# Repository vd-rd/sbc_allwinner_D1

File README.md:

### Features
 * CPU - Allwinner D1 processor (RISC-V C906 @ 1GHz)
 * RAM - 16Gb DDR3L max
 * microSD card slot
 * microUSB OTG port
 * RGMII interface for Ethernet
 * LCD interface
 * standard Apollo.IoT expansion header

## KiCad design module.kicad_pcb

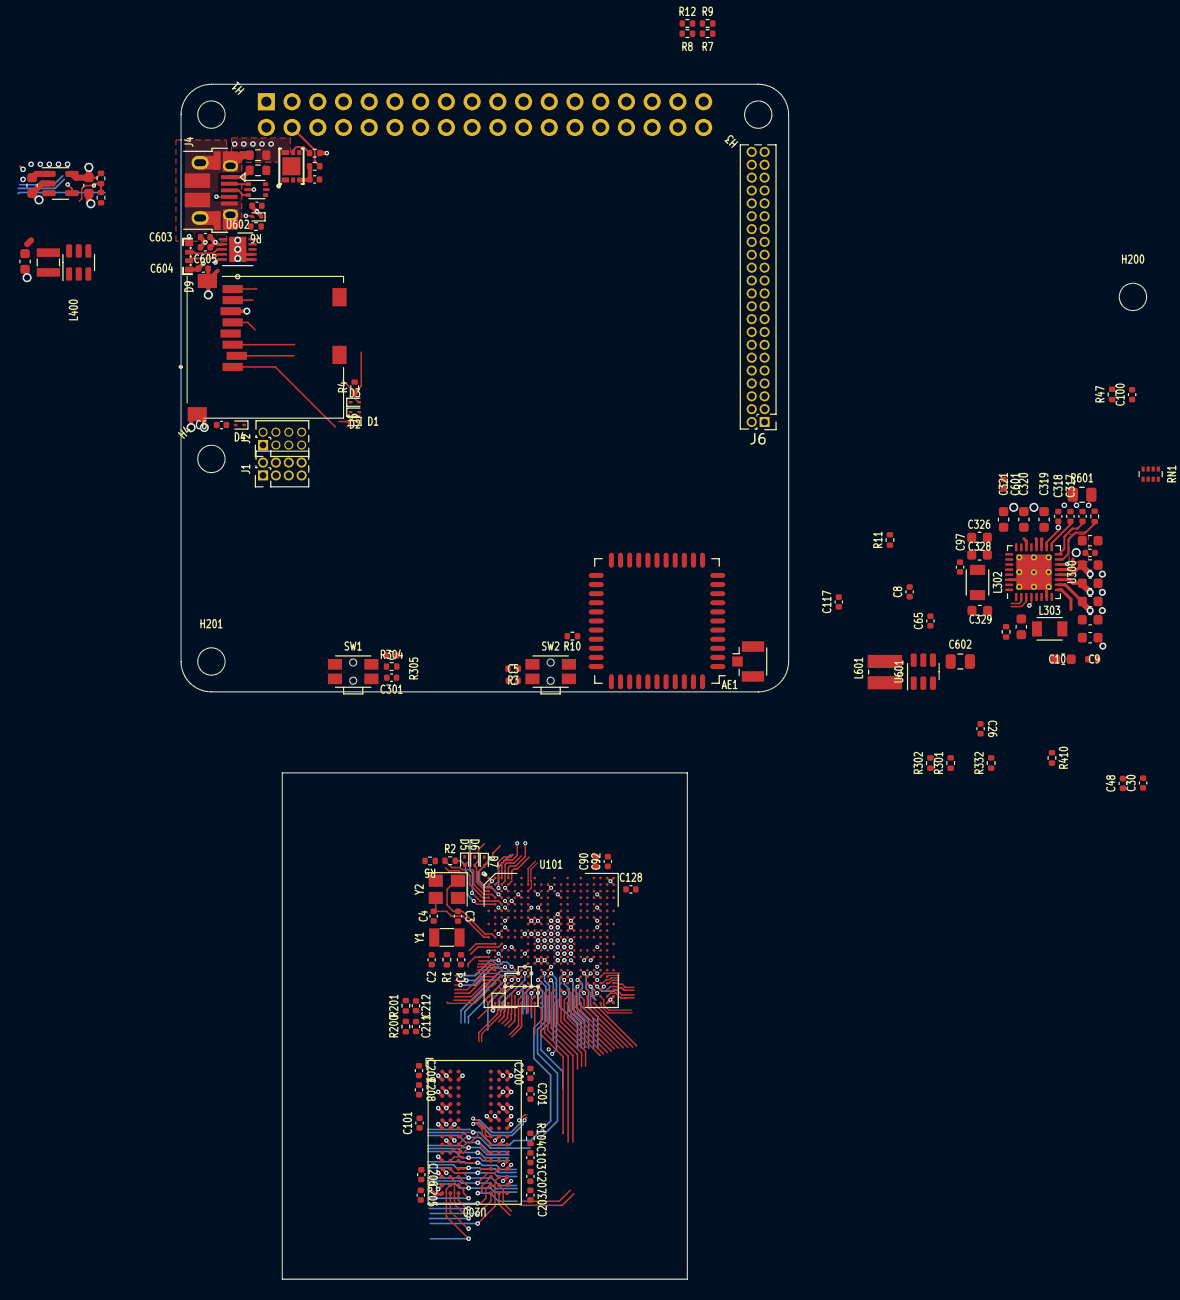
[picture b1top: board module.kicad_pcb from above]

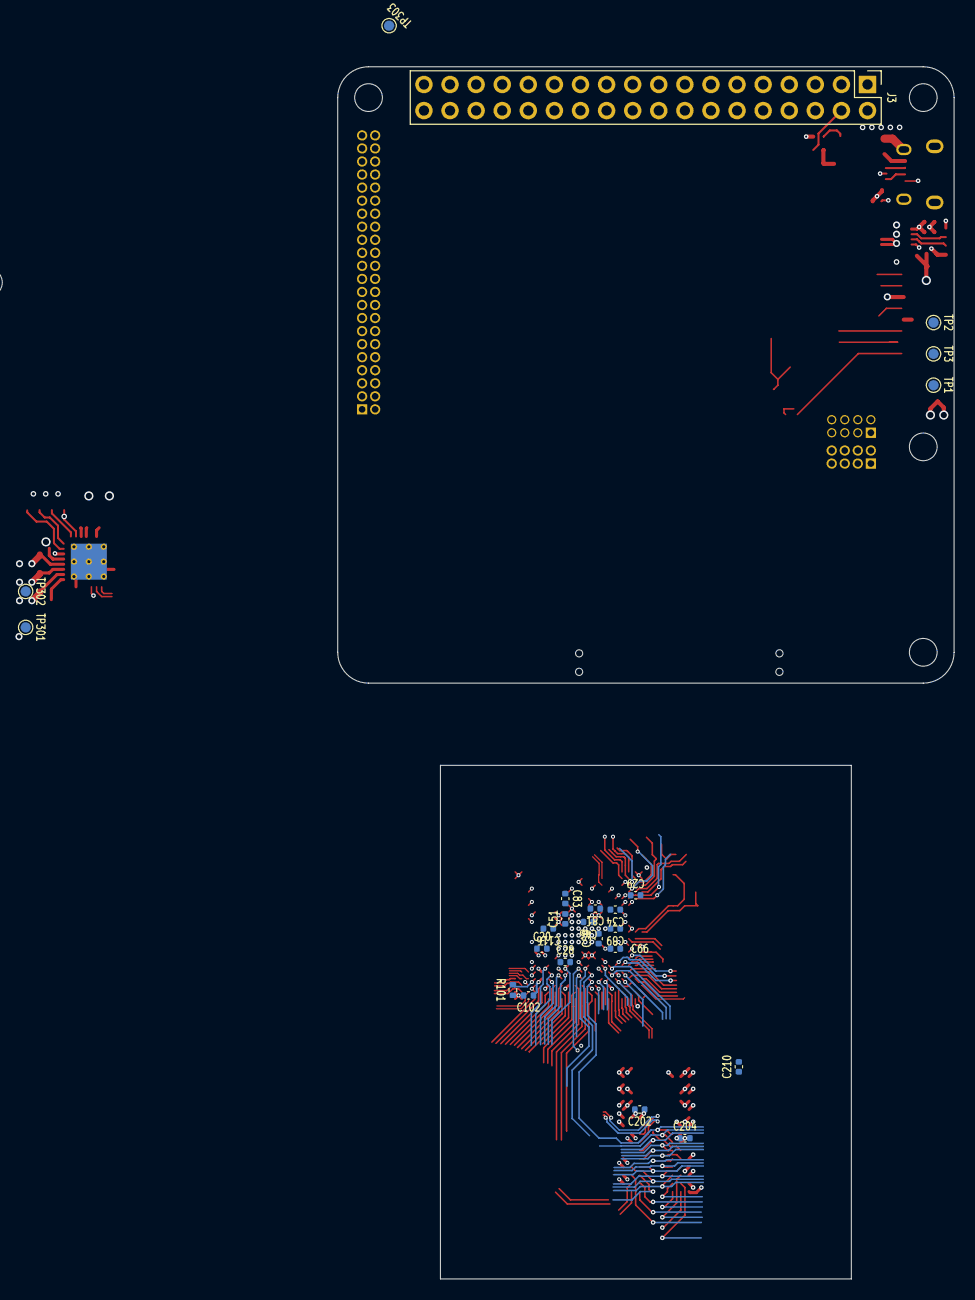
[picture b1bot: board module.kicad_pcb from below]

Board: 4 copper layers, 60.0 x 118.0 mm, 153 parts (24 on the bottom side), 179 nets.

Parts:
AE1: Antenna_Shield; U.FL_Hirose_U.FL-R-SMT-1_Vertical
C1, C2: 15pF; C_0402_1005Metric
C3, C4: 22pF; C_0402_1005Metric
C5, C7, C8, C10, C20, C26, C28, C29, C30, C34, C46, C48, C50, C51, C65, C66, C81, C83, C89, C97, C100, C101, C102, C103, C116, C117, C128, C200, C201, C202, C203, C204, C205, C206, C207, C208, C209, C210, C211, C212, C301, C501, C604, C3131: 100nF; C_0402_1005Metric
C6: 10uF; C_0402_1005Metric
C9, C309, C310, C312, C313: 4.7uF; C_0603_1608Metric
C90, C92: 470nF; C_0402_1005Metric
C305, C308, C311, C319, C320, C321, C326, C328, C329, C400, C410, C411: 10uF; C_0603_1608Metric
C316, C317, C318, C601, C603, C605: 1uF; C_0402_1005Metric
C602: C_Small; C_0805_2012Metric
D1, D2, D3, D4, D5, D6, D7: 3V3; D_SOD-923
D8: 5V; D_SOD-923
D9: LED_RGBA; rgb-1204
FB1, FB2: FerriteBead_Small; R_0603_1608Metric
H1, H3, H4, H200, H201: MountingHole; MountingHole_2.7mm_M2.5
J1, J2: Conn_01x08; PinHeader_2x04_P1.27mm_Vertical
J3: Conn_02x18_Odd_Even; PinHeader_2x18_P2.54mm_Vertical
J4: USB_B_Micro; USB_Micro-B_Amphenol_10103594-0001LF_Horizontal
J5: Micro_SD_Card_Det; MEM20610118800A
J6: Conn_02x22_Odd_Even; PinHeader_2x22_P1.27mm_Vertical
L302, L303: 4.7uH; L_TDK_NLV25_2.5x2.0mm
L400: L_Small; L_Wuerth_MAPI-2510
L601: 22uH; L_Wuerth_MAPI-3010
R1: 10M; R_0402_1005Metric
R2: 33; R_0402_1005Metric
R3, R305: 1k; R_0402_1005Metric
R4, R5, R6, R302, R303: 10k; R_0402_1005Metric
R7, R8, R9, R12, R304: 47k; R_0402_1005Metric
R10, R11: 22; R_0402_1005Metric
R47, R101, R104: 240; R_0402_1005Metric
R200, R201, R301: 2.2k; R_0402_1005Metric
R315: 200K; R_0402_1005Metric
R332: 10K; R_0402_1005Metric
R401: 976k; R_0402_1005Metric
R402: 562k; R_0402_1005Metric
R410: 100K; R_0402_1005Metric
R501: 330; R_0402_1005Metric
R502: 2.7k; R_0402_1005Metric
R601: 10; R_0805_2012Metric
RN1: 47k; R_Array_Concave_4x0402
SW1, SW2: SW_Push; SW_SPST_EVQP7C
TP1, TP2, TP3, TP301, TP302, TP303: TestPoint; TestPoint_Pad_D1.0mm
U1: USBLC6-2P6; SOT-666
U100: AP6255; lga44_12x12mm_P0.9
U101: D1; BGA-337_20x20_13.0x13.0mm
U200: DDR3L-x16; BGA-96_9x14mm_P0.8mm
U300: AXP173; VQFN-32-1EP_5x5mm_P0.5mm_EP3.5x3.5mm_ThermalVias
U400: MCP1640CH; SOT-23-6
U410: AP22811; SOT-23-5
U500: AP9211; DFN-2030-6
U601: AP3019; SOT-23-6
U602: IS31FL3193; DFN-10-1EP_3x3mm_P0.5mm_EP1.7x2.5mm
Y1: 32.768kHz; Crystal_SMD_3215-2Pin_3.2x1.5mm
Y2: 24M; Crystal_SMD_3225-4Pin_3.2x2.5mm

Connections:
+1V8_LDO: C20.1, C28.1, C50.1, C65.1, C89.1, C97.1, C301.1, R304.2, U101.J4 (VCC-EFUSE), U101.L7 (LDOA-OUT), U101.M17 (VCC-HDMI), U101.P14 (VDD18-DRAM), U101.R16 (VCC-LVDS)
+1V35: C200.1, C201.1, C202.1, C203.1, C204.1, C205.1, C206.1, C207.1, C208.1, C209.1, C210.1, C211.1, R200.1, U200.A1 (VDDQ), U200.A8 (VDDQ), U200.B2 (VDD), U200.C1 (VDDQ), U200.C9 (VDDQ), U200.D2 (VDDQ), U200.D9 (VDD), U200.E9 (VDDQ), U200.F1 (VDDQ), U200.G7 (VDD), U200.H2 (VDDQ), U200.H9 (VDDQ), U200.K2 (VDD), U200.K8 (VDD), U200.N1 (VDD), U200.N9 (VDD), U200.R1 (VDD), U200.R9 (VDD)
+3V0: C310.1, TP302.1, U300.10 (LDO2)
+3V3: C6.1, C29.1, C34.1, C66.1, C83.1, C128.1, C329.1, C603.1, C604.1, C605.1, D4.2 (A2), D9.4 (A), J3.2, J5.P4 (VDD), J6.43, L302.2, R4.2, R5.2, R6.2, R7.2, R9.2, R301.1, R302.1, R303.1, TP303.1, U101.C20 (VDD33), U101.D12 (HPLDOIN), U101.E4 (VCC-PG), U101.G4 (VCC-PC), U101.G17 (VCC-IO), U101.M7 (LDO-IN), U101.T16 (VCC-PD), U300.31 (DCDC1), U602.2 (VCC)
+3V3_LDO: C312.1, J6.8, U300.12 (LDO4)
+5V_USB: C7.1, C319.1, C411.1, FB2.2, U1.5 (VBUS), U300.19 (VBUS), U410.1 (OUT)
/cpu/hse-in: C4.1, U101.K1 (DXIN), Y2.3
/cpu/hse-out: C3.1, U101.K2 (DXOUT), Y2.1
/cpu/lse-in: C1.1, R1.1, U101.L2 (X32KIN), Y1.1
/cpu/lse-out: C2.1, R1.2, U101.L3 (X32KOUT), Y1.2
/cpu/vcc-dram: C30.1, C48.1
/cpu/vra1: C92.1, U101.B19 (VRA1)
/cpu/vra2: C90.1, U101.B18 (VRA2)
/io/uart0: D5.2 (A2), J5.P5 (CLK), R2.2, TP1.1
/io/usb+: J4.3 (D+), U1.3 (I/O2)
/io/usb-: J4.2 (D-), U1.1 (I/O1)
/io/usb_gnd: FB1.1, J4.5 (GND), J4.6 (Shield)
/memory/ddr-a0: U101.V13 (SA0), U200.N3 (A0)
/memory/ddr-a1: U101.W13 (SA1), U200.P7 (A1)
/memory/ddr-a2: U101.V14 (SA2), U200.P3 (A2)
/memory/ddr-a3: U101.U13 (SA3), U200.N2 (A3)
/memory/ddr-a4: U101.U15 (SA4), U200.P8 (A4)
/memory/ddr-a5: U101.V11 (SA5), U200.P2 (A5)
/memory/ddr-a6: U101.W11 (SA6), U200.R8 (A6)
/memory/ddr-a7: U101.Y13 (SA7), U200.R2 (A7)
/memory/ddr-a8: U101.W14 (SA8), U200.T8 (A8)
/memory/ddr-a9: U101.Y15 (SA9), U200.R3 (A9)
/memory/ddr-a10: U101.W12 (SA10), U200.L7 (A10/AP)
/memory/ddr-a11: U101.W15 (SA11), U200.R7 (A11)
/memory/ddr-a12: U101.W16 (SA12), U200.N7 (A12/~BC)
/memory/ddr-a13: U101.R15 (SA13), U200.T3 (A13)
/memory/ddr-a14: U101.V16 (SA14), U200.T7 (A14)
/memory/ddr-a15: U101.T15 (SA15), U200.M7 (A15(nc))
/memory/ddr-ba0: U101.V10 (SBA0), U200.M2 (BA0)
/memory/ddr-ba1: U101.W10 (SBA1), U200.N8 (BA1)
/memory/ddr-ba2: U101.Y11 (SBA2), U200.M3 (BA2)
/memory/ddr-cas: U101.T9 (SCAS), U200.K3 (~CAS)
/memory/ddr-cke0: U101.W9 (SCKE0), U200.K9 (CKE)
/memory/ddr-cs0: U101.R12 (SCS0), U200.L2 (~CS)
/memory/ddr-d0: U101.W7 (SDQ0), U200.E3 (DQL0)
/memory/ddr-d1: U101.V7 (SDQ1), U200.F7 (DQL1)
/memory/ddr-d2: U101.W8 (SDQ2), U200.F2 (DQL2)
/memory/ddr-d3: U101.V8 (SDQ3), U200.F8 (DQL3)
/memory/ddr-d4: U101.W4 (SDQ4), U200.H3 (DQL4)
/memory/ddr-d5: U101.Y4 (SDQ5), U200.H7 (DQL7)
/memory/ddr-d6: U101.V5 (SDQ6), U200.G2 (DQL6)
/memory/ddr-d7: U101.W5 (SDQ7), U200.H8 (DQL5)
/memory/ddr-d8: U101.U4 (SDQ8), U200.D7 (DQU0)
/memory/ddr-d9: U101.U7 (SDQ9), U200.C3 (DQU1)
/memory/ddr-d10: U101.U5 (SDQ10), U200.C8 (DQU2)
/memory/ddr-d11: U101.T6 (SDQ11), U200.C2 (DQU3)
/memory/ddr-d12: U101.U6 (SDQ12), U200.A7 (DQU4)
/memory/ddr-d13: U101.R7 (SDQ13), U200.B8 (DQU6)
/memory/ddr-d14: U101.T4 (SDQ14), U200.A3 (DQU7)
/memory/ddr-d15: U101.R6 (SDQ15), U200.A2 (DQU5)
/memory/ddr-dm0: U101.Y8 (SDQM0), U200.E7 (DML)
/memory/ddr-dm1: U101.W2 (SDQM1), U200.D3 (DMU)
/memory/ddr-dqs0+: U101.W6 (SDQS0), U200.F3 (DQSL)
/memory/ddr-dqs0-: U101.Y6 (~SDQS0), U200.G3 (~DQSL)
/memory/ddr-dqs1+: U101.W3 (SDQS1), U200.C7 (DQSU)
/memory/ddr-dqs1-: U101.Y3 (~SDQS1), U200.B7 (~DQSU)
/memory/ddr-odt0: U101.T12 (ODT0), U200.K1 (ODT)
/memory/ddr-ras: U101.U9 (SRAS), U200.J3 (~RAS)
/memory/ddr-rst: U101.Y17 (SRST), U200.T2 (~RESET)
/memory/ddr-sck+: U101.T10 (SCK), U200.J7 (CK)
/memory/ddr-sck-: U101.U10 (~SCK), U200.K7 (~CK)
/memory/ddr-we: U101.R9 (SWE), U200.L3 (~WE)
/memory/svref: C101.1, C102.1, C103.1, C211.2, C212.1, R200.2, R201.1, U101.U16 (SVREF0), U200.H1 (VREFDQ), U200.M8 (VREFCA)
/power/vint: C317.1, U300.17 (VINT)
ACIN: C320.1, J3.3, U300.20 (ACIN)
BAT_GND: C501.2, J3.5, U500.1 (S1), U500.2 (VSS)
BAT_NTC: J3.6, U300.24 (TS)
BTN: R304.1, R305.2, U101.B12 (LRADC)
CLK32K-OUT: R10.1, U101.F7 (PG16)
GND: AE1.2 (Shield), C1.2, C2.2, C3.2, C4.2, C5.2, C6.2, C7.2, C8.2, C9.2, C10.2, C20.2, C26.2, C28.2, C29.2, C30.2, C34.2, C46.2, C48.2, C50.2, C51.2, C65.2, C66.2, C81.2, C83.2, C89.2, C90.2, C92.2, C97.2, C101.2, C102.2, C103.2, C116.2, C117.2, C128.2, C200.2, C201.2, C202.2, C203.2, C204.2, C205.2, C206.2, C207.2, C208.2, C209.2, C210.2, C212.2, C301.2, C305.2, C308.2, C309.2, C310.2, C311.2, C312.2, C313.2, C316.2, C317.2, C318.2, C319.2, C320.2, C321.2, C326.2, C328.2, C329.2, C400.2, C410.2, C411.2, C601.2, C602.2, C603.2, C604.2, C605.2, C3131.2, D1.1 (A1), D2.1 (A1), D3.1 (A1), D4.1 (A1), D5.1 (A1), D6.1 (A1), D7.1 (A1), D8.1 (A1), FB1.2, J1.1, J2.1, J3.1, J3.14, J3.23, J3.36, J5.G1 (SHIELD), J5.G2 (SHIELD), J5.P6 (VSS), J6.1, J6.10, J6.11, J6.36, J6.37, J6.44, R8.1, R12.1, R47.1, R101.1, R104.1, R201.2, R315.2, R402.2, R410.2, R502.2, R601.2, SW1.2, SW2.2, TP3.1, U1.2 (GND), U100.1 (GND), U100.3 (GND), U100.20 (GND), U100.31 (GND), U100.33 (GND), U100.36 (GND), U101.A1 (GND), U101.A2 (GND), U101.A15 (GND), U101.A19 (GND), U101.A20 (GND), U101.B1 (GND), U101.B10 (GND), U101.B20 (GND), U101.C4 (GND), U101.C8 (GND), U101.C10 (GND), U101.D18 (AGND), U101.E5 (GND), U101.E9 (GND-TVIN), U101.F3 (GND), U101.F9 (GND), U101.F12 (GND), U101.F18 (GND), U101.G10 (GND), U101.G11 (GND), U101.G12 (GND), U101.H1 (GND), U101.H2 (GND), U101.H10 (GND), U101.H11 (GND), U101.H12 (GND), U101.H18 (GND), U101.J3 (GND), U101.J6 (GND), U101.J7 (GND), U101.J8 (GND), U101.J9 (GND), U101.J10 (GND), U101.J11 (GND), U101.J12 (GND), U101.K3 (GND), U101.K6 (GND), U101.K7 (GND), U101.K8 (GND), U101.K9 (GND), U101.K10 (GND), U101.K11 (GND), U101.K12 (GND), U101.K13 (GND), U101.K14 (GND), U101.L8 (GND), U101.L9 (GND), U101.L10 (GND), U101.L11 (GND), U101.L12 (GND), U101.L13 (GND), U101.L14 (GND), U101.L18 (GND), U101.M3 (GND), U101.M5 (GND), U101.M8 (GND), U101.M9 (GND), U101.M10 (GND), U101.M11 (GND), U101.M12 (GND), U101.M13 (GND), U101.M14 (GND), U101.N11 (GND), U101.N12 (GND), U101.N13 (GND), U101.N14 (GND), U101.N15 (GND), U101.N18 (GND), U101.P7 (GND), U101.P11 (GND), U101.P12 (GND), U101.P13 (GND), U101.R10 (GND), U101.R18 (GND), U101.T5 (GND), U101.T7 (GND), U101.T13 (GND), U101.V2 (GND), U101.V3 (GND), U101.V4 (GND), U101.V6 (GND), U101.V9 (GND), U101.V12 (GND), U101.V15 (GND), U101.V17 (GND), U101.W1 (GND), U101.W17 (GND), U101.W20 (GND), U101.Y1 (GND), U101.Y2 (GND), U101.Y19 (GND), U101.Y20 (GND), U200.A9 (VSS), U200.B1 (VSSQ), U200.B3 (VSS), U200.B9 (VSSQ), U200.D1 (VSSQ), U200.D8 (VSSQ), U200.E1 (VSS), U200.E2 (VSSQ), U200.E8 (VSSQ), U200.F9 (VSSQ), U200.G1 (VSSQ), U200.G8 (VSS), U200.G9 (VSSQ), U200.J2 (VSS), U200.J8 (VSS), U200.M1 (VSS), U200.M9 (VSS), U200.P1 (VSS), U200.P9 (VSS), U200.T1 (VSS), U200.T9 (VSS), U300.7 (PGND2), U300.30 (PGND1), U300.33 (EP), U400.2 (GND), U410.2 (GND), U500.6 (S2), U601.2 (GND), U602.6 (GND), U602.7 (AD), U602.11 (GND)
GPIO1: J3.13, U101.Y18 (PD22)
GPIO2: J3.20, U101.D6 (PG13)
I2C-SCL: J3.17, R302.2, U101.C6 (PG10), U300.2 (SCK), U602.8 (SCL)
I2C-SDA: J3.18, R301.2, U101.D4 (PG11), U300.1 (SDA), U602.9 (SDA)
IPS: C305.1, C311.1, C313.1, C326.1, C328.1, C400.1, C601.1, C3131.1, L400.2, L601.1, U300.5 (VIN2), U300.11 (LDOIN), U300.13 (APS), U300.25 (IPSOUT), U300.26 (IPSOUT), U300.28 (VIN1), U400.6 (VIN), U601.6 (VIN)
LCD-HSYNC: J6.40, U101.W18 (PD20)
LCD-VSYNC: J6.41, U101.V18 (PD21)
LDO3: C309.1, U300.9 (LDO3)
LED_A: C602.1, U601.5 (Vout)
LED_K: R601.1, U601.3 (FB)
LVDS0_CK+: J6.25, U101.T19 (PD6)
LVDS0_CK-: J6.24, U101.T18 (PD7)
LVDS0_V0+: J6.33, U101.W19 (PD0)
LVDS0_V0-: J6.32, U101.V20 (PD1)
LVDS0_V1+: J6.31, U101.V19 (PD2)
LVDS0_V1-: J6.30, U101.U20 (PD3)
LVDS0_V2+: J6.29, U101.U19 (PD4)
LVDS0_V2-: J6.28, U101.U18 (PD5)
LVDS0_V3+: J6.23, U101.R20 (PD8)
LVDS0_V3-: J6.22, U101.R19 (PD9)
LVDS1_CK+: J6.13, U101.N20 (PD16)
LVDS1_CK-: J6.12, U101.N19 (PD17)
LVDS1_V0+: J6.21, U101.T17 (PD10)
LVDS1_V0-: J6.20, U101.R17 (PD11)
LVDS1_V1+: J6.17, U101.P19 (PD12)
LVDS1_V1-: J6.16, U101.P18 (PD13)
LVDS1_V2+: J6.15, U101.N17 (PD14)
LVDS1_V2-: J6.14, U101.N16 (PD15)
LVDS1_V3+: J6.39, U101.M19 (PD18)
LVDS1_V3-: J6.38, U101.M18 (PD19)
NMI: R332.2, U101.N3 (NMI), U300.32 (IRQ)
unnamed: AE1.1 (A), U100.2 (WL_BT_ANT)
unnamed: C8.1, U100.22 (VDDIO)
unnamed: C9.1, C10.1, U100.9 (VBAT)
unnamed: C316.1, U300.16 (VREF)
unnamed: C410.1, R401.1, U400.5 (VOUT), U410.5 (IN)
unnamed: C501.1, R501.2, U500.3 (VDD)
unnamed: D9.1 (RK), U602.3 (OUT1)
unnamed: D9.2 (GK), U602.4 (OUT2)
unnamed: D9.3 (BK), U602.5 (OUT3)
unnamed: FB2.1, J4.1 (VBUS)
unnamed: L302.1, U300.29 (LX1)
unnamed: L303.1, U300.6 (LX2)
unnamed: L400.1, U400.1 (SW)
unnamed: L601.2, U601.1 (SW)
unnamed: R3.1, SW2.1
unnamed: R10.2, U100.24 (LPO)
unnamed: R11.2, U100.17 (SDIO_CLK)
unnamed: R101.2, U101.U17 (SZQ)
unnamed: R104.2, U200.L8 (ZQ)
unnamed: R305.1, SW1.1
unnamed: R315.1, U300.15 (BIAS)
unnamed: R401.2, R402.1, U400.4 (VFB)
unnamed: R502.1, U500.5 (VM)
unnamed: U101.C18 (AVCC), U101.C19 (ALDO)
unnamed: U101.D10 (HPVCC), U101.E12 (HPLDO)
unnamed: U101.N8 (VCC-DRAM), U101.N9 (VCC-DRAM), U101.N10 (VCC-DRAM), U101.P8 (VCC-DRAM), U101.P9 (VCC-DRAM), U101.P10 (VCC-DRAM)
PMU-VBUSEN: R410.1, U300.4 (~VBUSEN), U400.3 (EN), U410.4 (EN)
PON: C5.1, R3.2, U300.14 (PWRON)
RGMII-RX0: J1.4, U101.U1 (PE1)
RGMII-RX1: J1.5, U101.U2 (PE2)
RGMII-RX2: J1.6, U101.R5 (PE12)
RGMII-RX3: J1.7, U101.R4 (PE13)
RGMII-RXCK: J1.2, U101.R2 (PE7)
RGMII-RXCTL: J1.3, U101.V1 (PE0)
RGMII-TX0: J2.4, U101.T2 (PE4)
RGMII-TX1: J2.5, U101.T3 (PE5)
RGMII-TX2: J2.6, U101.P3 (PE10)
RGMII-TX3: J2.7, U101.N1 (PE11)
RGMII-TXCK: J2.2, U101.U3 (PE3)
RGMII-TXCTL: J2.3, U101.R1 (PE6)
RMII-MDC: J1.8, U101.R3 (PE8)
RMII-MDIO: J2.8, U101.P2 (PE9)
SDC0-CLK: R2.1, U101.D2 (PF2)
SDC0-CMD: D3.2 (A2), J5.P3 (CMD), R4.1, U101.D1 (PF3)
SDC0-D0: D6.2 (A2), J5.P7 (DAT0), U101.C1 (PF1)
SDC0-D1: D7.2 (A2), J5.P8 (DAT1), U101.C2 (PF0)
SDC0-D2: D1.2 (A2), J5.P1 (DAT2), U101.E2 (PF5)
SDC0-D3: D2.2 (A2), J5.P2 (DAT3/CD), TP2.1, U101.E3 (PF4)
SDC0-DET: J5.CD1 (DET_A), J5.CD2 (DET_B), R5.1, U101.D3 (PF6)
SDC1-CLK: R11.1, U101.B2 (PG0)
SDC1-CMD: U100.16 (SDIO_CMD), U101.B3 (PG1)
SDC1-D0: U100.18 (SDIO_DATA0), U101.A3 (PG2)
SDC1-D1: U100.19 (SDIO_DATA1), U101.C3 (PG3)
SDC1-D2: U100.14 (SDIO_DATA2), U101.A4 (PG4)
SDC1-D3: U100.15 (SDIO_DATA3), U101.B4 (PG5)
SDIO-24M: U100.10 (XTAL_IN), U101.J2 (REFCLK-OUT)
SPI-CLK: J3.25, U101.G3 (PC2)
SPI-CS: J3.26, U101.G2 (PC3)
SPI-MISO: J3.28, R9.1, R12.2, U101.F5 (PC5)
SPI-MOSI: J3.27, R7.1, R8.2, U101.H3 (PC4)
UART0-RX: J3.12, U101.J17 (PB1)
UART0-TX: J3.11, U101.J16 (PB0)
UART1-RX: J3.16, U101.G16 (PB9)
UART1-TX: J3.15, U101.G15 (PB8)
UART2-RX: J3.22, U101.G5 (PC7)
UART2-TX: J3.21, U101.G6 (PC6)
USB-D+: U1.4 (I/O2), U101.B7 (USB0-DP)
USB-D-: U1.6 (I/O1), U101.C7 (USB0-DM)
USB-ID: D8.2 (A2), J4.4 (ID), R6.1
VBAT: C321.1, J3.4, R501.1, U300.21 (BAT), U300.22 (BAT)
VCC_RTC: C26.1, C318.1, U101.K5 (VCC-RTC), U300.18 (LDO1)
VDD_SYS: C46.1, C51.1, C81.1, C116.1, C117.1, C308.1, L303.2, TP301.1, U101.G7 (VDD-CPU), U101.G8 (VDD-CPU), U101.G13 (VDD-SYS), U101.G14 (VDD-SYS), U101.H7 (VDD-CPU), U101.H8 (VDD-CPU), U101.H9 (VDD-CPU), U101.H13 (VDD-SYS), U101.H14 (VDD-SYS), U101.J13 (VDD-SYS), U101.J14 (VDD-SYS), U300.8 (DCDC2)
~RST: J3.7, R303.2, U101.M2 (RESET), U300.3 (POWOK)

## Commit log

2021-12-29 initial bringup
2021-12-30 ddr routing
2022-01-11 test new ddr layout
2022-01-14 [wip] new dram routing
2022-01-25 small ddr tweaks
2022-01-25 more ddr routing
2022-01-30 add new lcd connector
2022-02-11 add layout rules
2022-06-29 update project
